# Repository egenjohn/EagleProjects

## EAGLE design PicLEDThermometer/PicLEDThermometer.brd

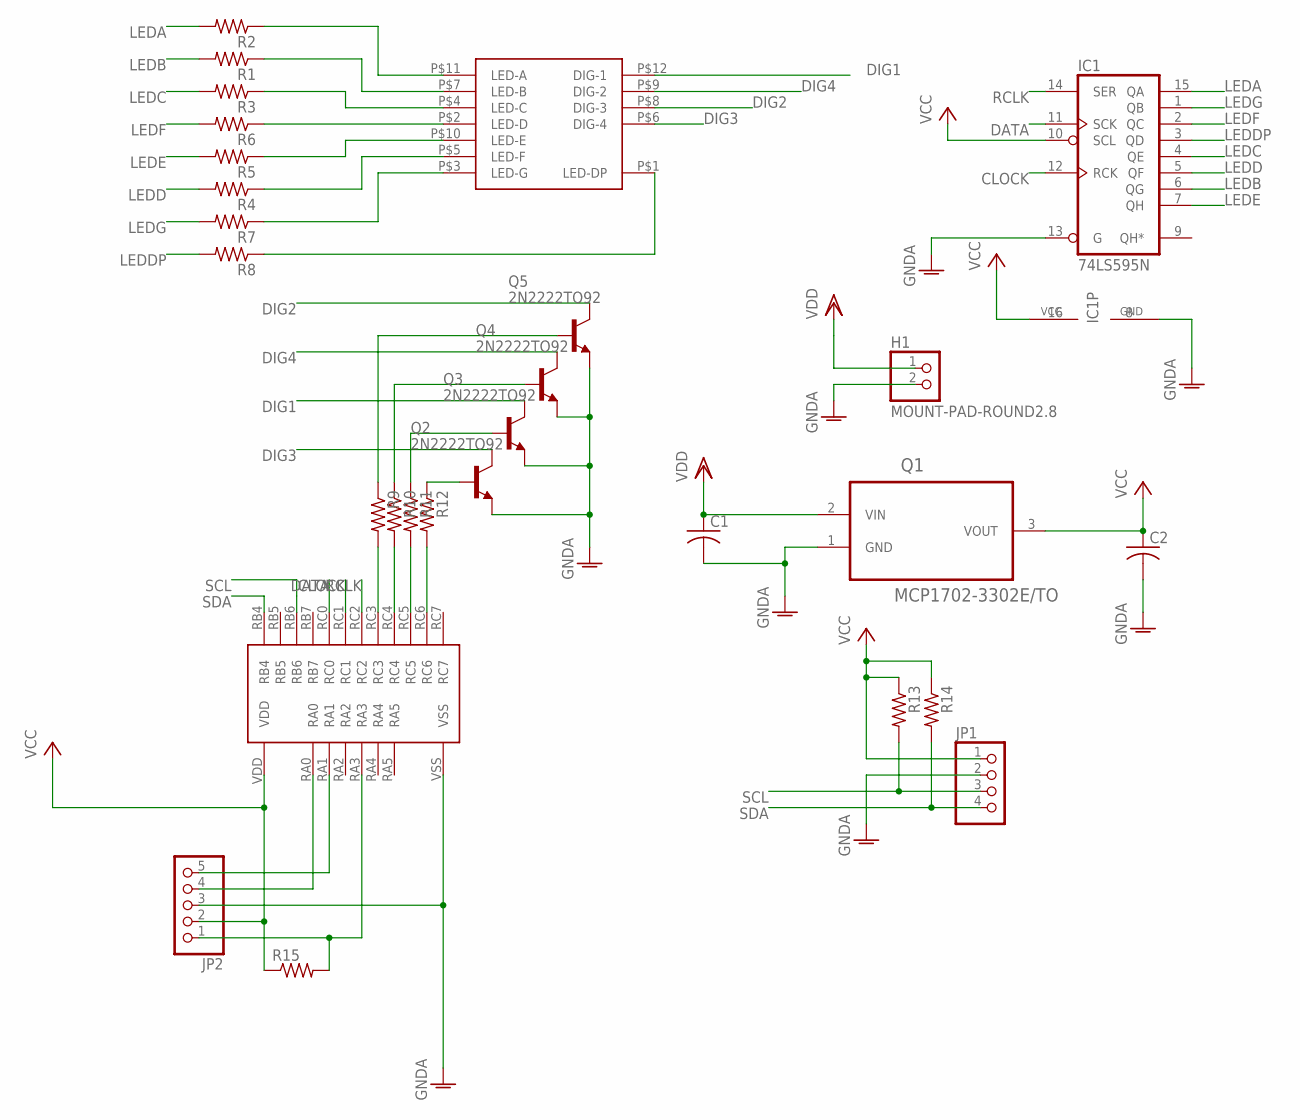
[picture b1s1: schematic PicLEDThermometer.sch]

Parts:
C1, C2: C-US025-030X050; C025-030X050
H1: MOUNT-PAD-ROUND2.8; 1X02
IC1: 74LS595N; DIL16
JP1: PINHD-1X4; 1X04
JP2: PINHD-1X5; 1X05
Q1: MCP1702-3302E/TO; TO127P254X533-3
Q2, Q3, Q4, Q5: 2N2222TO92; TO92-LINE
R1, R2, R3, R4, R5, R6, R7, R8, R9, R10, R11, R12, R13, R14, R15: R-US_0207/10; 0207/10
U$1: FYQ-5641
U$2: PIC16F1707

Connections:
CLOCK: IC1.12 (RCK), U$2.RC1
DATA: IC1.11 (SCK), U$2.RC0
DIG1: Q3.COL (C), U$1.P$12 (DIG-1)
DIG2: Q5.COL (C), U$1.P$8 (DIG-3)
DIG3: Q2.COL (C), U$1.P$6 (DIG-4)
DIG4: Q4.COL (C), U$1.P$9 (DIG-2)
GNDA: C1.2, C2.2, H1.2, IC1.8 (GND), IC1.13 (G), JP1.2, JP2.3, Q1.1 (GND), Q2.EMIT (E), Q3.EMIT (E), Q4.EMIT (E), Q5.EMIT (E), U$2.VSS
LEDA: IC1.15 (QA), R2.2
LEDB: IC1.6 (QG), R1.2
LEDC: IC1.4 (QE), R3.2
LEDD: IC1.5 (QF), R4.2
LEDDP: IC1.3 (QD), R8.2
LEDE: IC1.7 (QH), R5.2
LEDF: IC1.2 (QC), R6.2
LEDG: IC1.1 (QB), R7.2
unnamed: R2.1, U$1.P$11 (LED-A)
unnamed: R1.1, U$1.P$7 (LED-B)
unnamed: R3.1, U$1.P$4 (LED-C)
unnamed: R6.1, U$1.P$2 (LED-D)
unnamed: R5.1, U$1.P$10 (LED-E)
unnamed: R4.1, U$1.P$5 (LED-F)
unnamed: R7.1, U$1.P$3 (LED-G)
unnamed: JP2.1, R15.2, U$2.RA3
unnamed: JP2.4, U$2.RA0
unnamed: JP2.5, U$2.RA1
unnamed: R12.2, U$2.RC6
unnamed: R8.1, U$1.P$1 (LED-DP)
unnamed: R11.2, U$2.RC5
unnamed: R10.2, U$2.RC4
unnamed: R9.2, U$2.RC3
unnamed: Q2.BASE (B), R12.1
unnamed: Q3.BASE (B), R11.1
unnamed: Q4.BASE (B), R10.1
unnamed: Q5.BASE (B), R9.1
RCLK: IC1.14 (SER), U$2.RC2
SCL: JP1.3, R13.2, U$2.RB6
SDA: JP1.4, R14.2, U$2.RB4
VCC: C2.1, IC1.10 (SCL), IC1.16 (VCC), JP1.1, JP2.2, Q1.3 (VOUT), R13.1, R14.1, R15.1, U$2.VDD
VDD: C1.1, H1.1, Q1.2 (VIN)

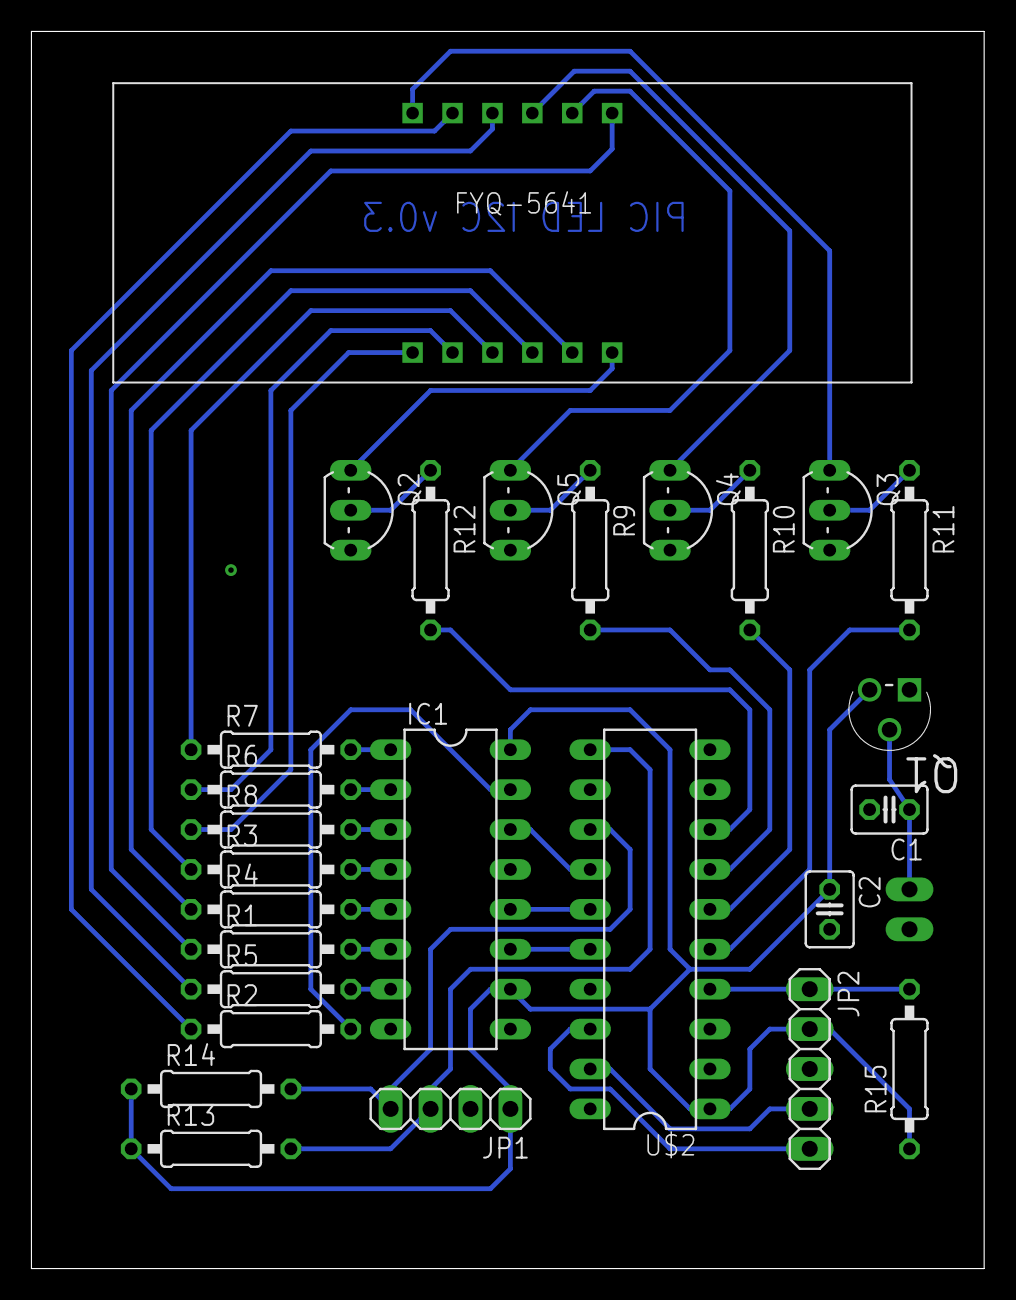
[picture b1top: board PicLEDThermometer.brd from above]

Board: 2 copper layers, 60.6 x 78.7 mm, 28 parts (1 on the bottom side), 39 nets.

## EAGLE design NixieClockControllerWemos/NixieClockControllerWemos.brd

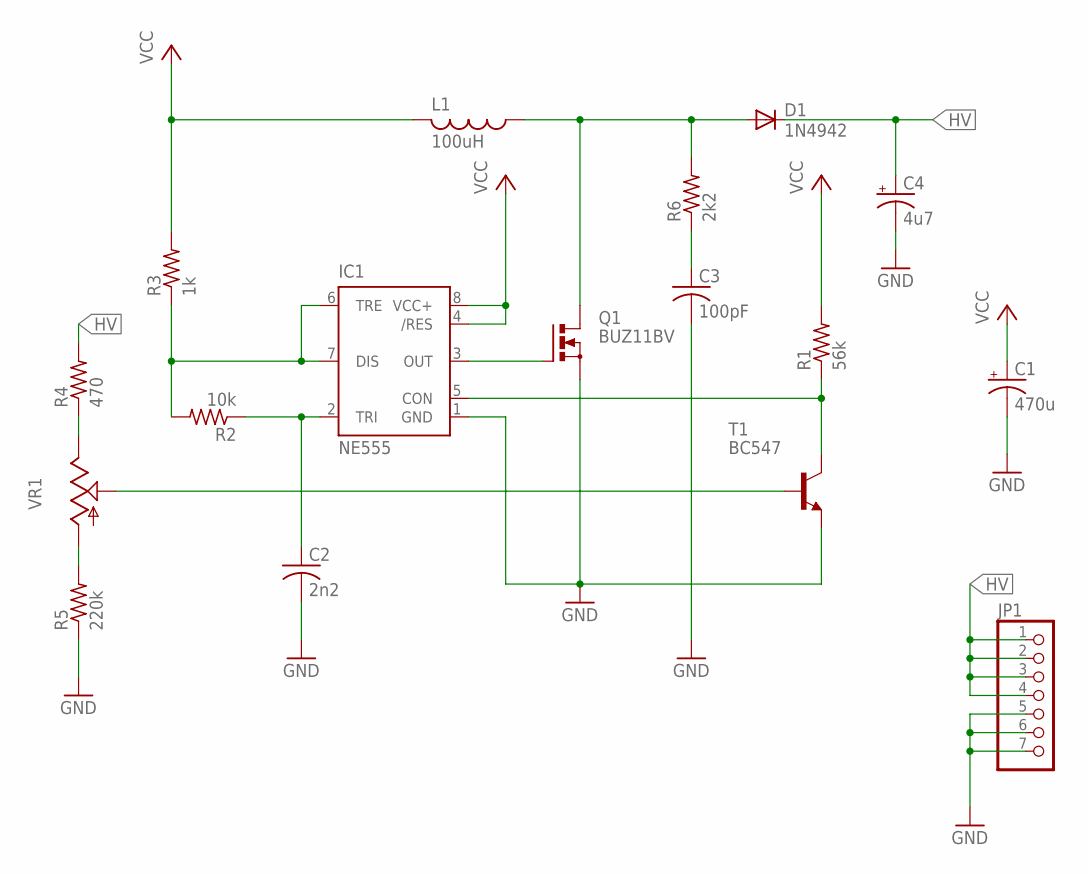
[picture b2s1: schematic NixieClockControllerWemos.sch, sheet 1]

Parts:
C1: 470u; E5-13
C2: 2n2; C050-025X075
C3: 100pF; C050-025X075
C4: 4u7; E3,5-8
D1: 1N4942; DO41-10
IC1: NE555; DIL-08
JP1: PINHD-1X7; 1X07
L1: 100uH; RLB0914
Q1: BUZ11BV; TO220BV
R1: 56k; 0207/10
R2: 10k; 0207/10
R3: 1k; 0207/10
R4: 470; 0207/10
R5: 220k; 0207/10
R6: 2k2; 0207/10
T1: BC547; TO92
VR1: TRIM_US-B25P; B25P

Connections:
GND: C1.-, C2.2, C3.2, C4.-, IC1.1 (GND), JP1.5, JP1.6, JP1.7, Q1.S, R5.1, T1.1 (E); also elsewhere on the board
HV: C4.+, D1.C, JP1.1, JP1.2, JP1.3, JP1.4, R4.2
unnamed: IC1.3 (OUT), Q1.G
unnamed: D1.A, L1.1, Q1.D, R6.2
unnamed: IC1.6 (TRE), IC1.7 (DIS), R2.2, R3.1
unnamed: R4.1, VR1.E
unnamed: IC1.5 (CON), R1.1, T1.3 (C)
unnamed: R5.2, VR1.A
unnamed: T1.2 (B), VR1.S
unnamed: C3.1, R6.1
unnamed: C2.1, IC1.2 (TRI), R2.1
VCC: C1.+, IC1.4 (/RES), IC1.8 (VCC+), L1.2, R1.2, R3.2; also elsewhere on the board

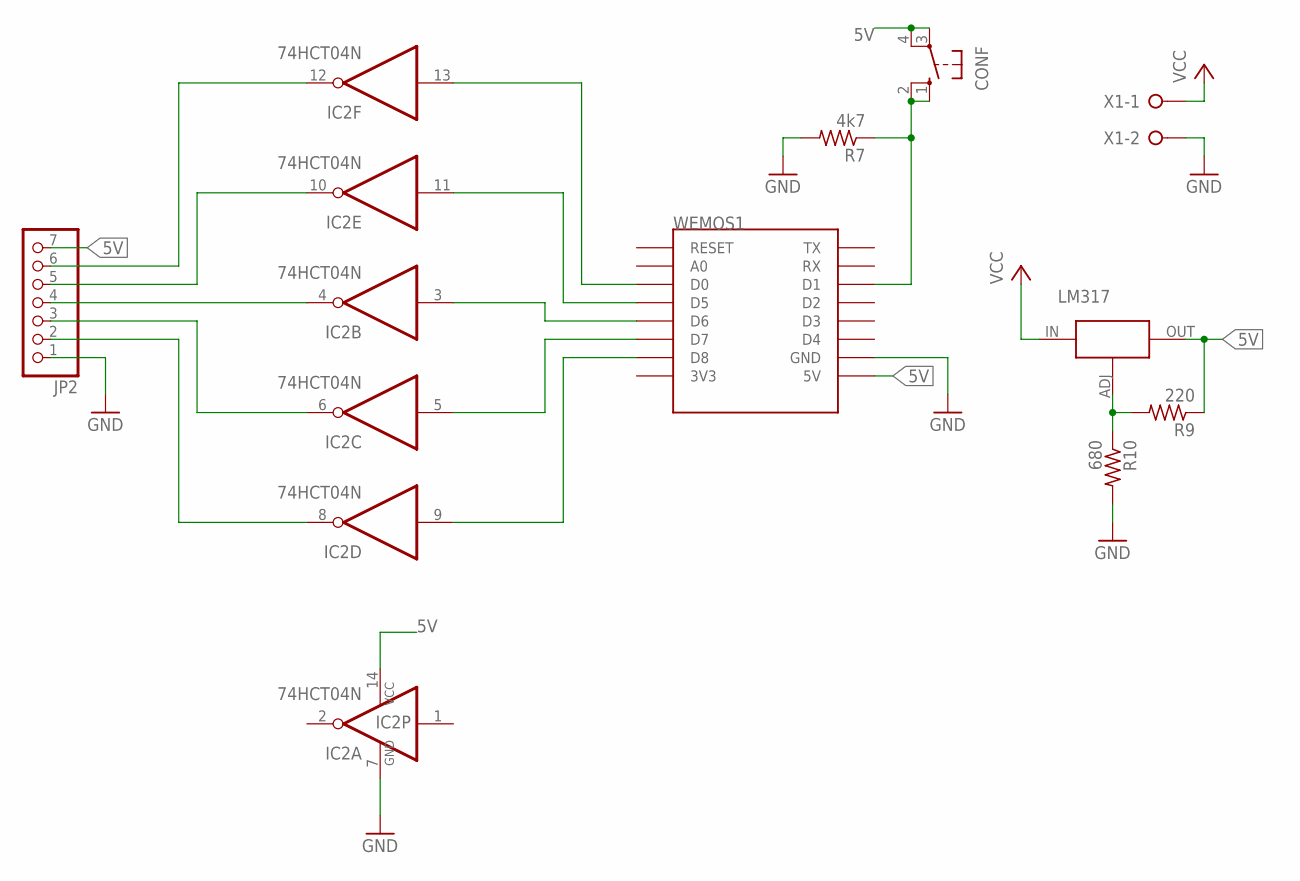
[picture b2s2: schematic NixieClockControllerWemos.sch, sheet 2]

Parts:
CONF: 10-XX; B3F-10XX
IC2: 74HCT04N; DIL14
JP2: PINHD-1X7; 1X07
R7: 4k7; 0207/10
R9: 220; 0207/10
R10: 680; 0207/10
U$3: LM317-TO220; LM317-TO220AV
WEMOS1: WEMOS-D1-MINI
X1: W237-02P; W237-132

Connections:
5V: CONF.3, CONF.4 (P1), IC2.14 (VCC), JP2.7, R9.1, U$3.OUT (VO), WEMOS1.5V
GND: IC2.7 (GND), JP2.1, R7.2, R10.2, WEMOS1.GND, X1.2; also elsewhere on the board
unnamed: IC2.12 (O), JP2.6
unnamed: IC2.10 (O), JP2.5
unnamed: R9.2, R10.1, U$3.ADJ
unnamed: IC2.4 (O), JP2.4
unnamed: IC2.6 (O), JP2.3
unnamed: IC2.8 (O), JP2.2
unnamed: CONF.1 (S), CONF.2 (S1), R7.1, WEMOS1.D1
unnamed: IC2.13 (I), WEMOS1.D0
unnamed: IC2.11 (I), WEMOS1.D5
unnamed: IC2.3 (I), WEMOS1.D6
unnamed: IC2.5 (I), WEMOS1.D7
unnamed: IC2.9 (I), WEMOS1.D8
VCC: U$3.IN (VI), X1.1; also elsewhere on the board

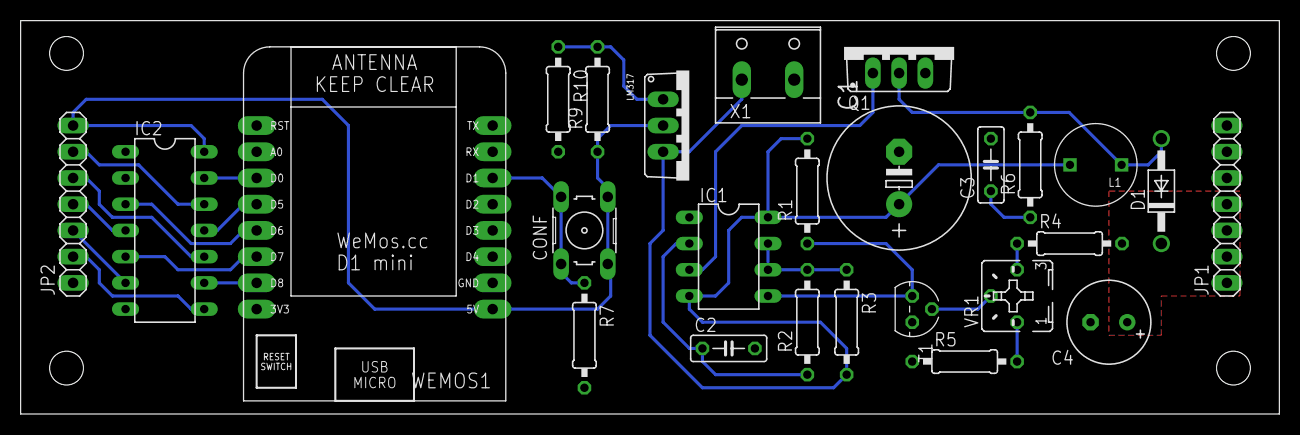
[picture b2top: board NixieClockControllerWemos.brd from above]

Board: 2 copper layers, 121.9 x 38.1 mm, 26 parts (0 on the bottom side), 25 nets.

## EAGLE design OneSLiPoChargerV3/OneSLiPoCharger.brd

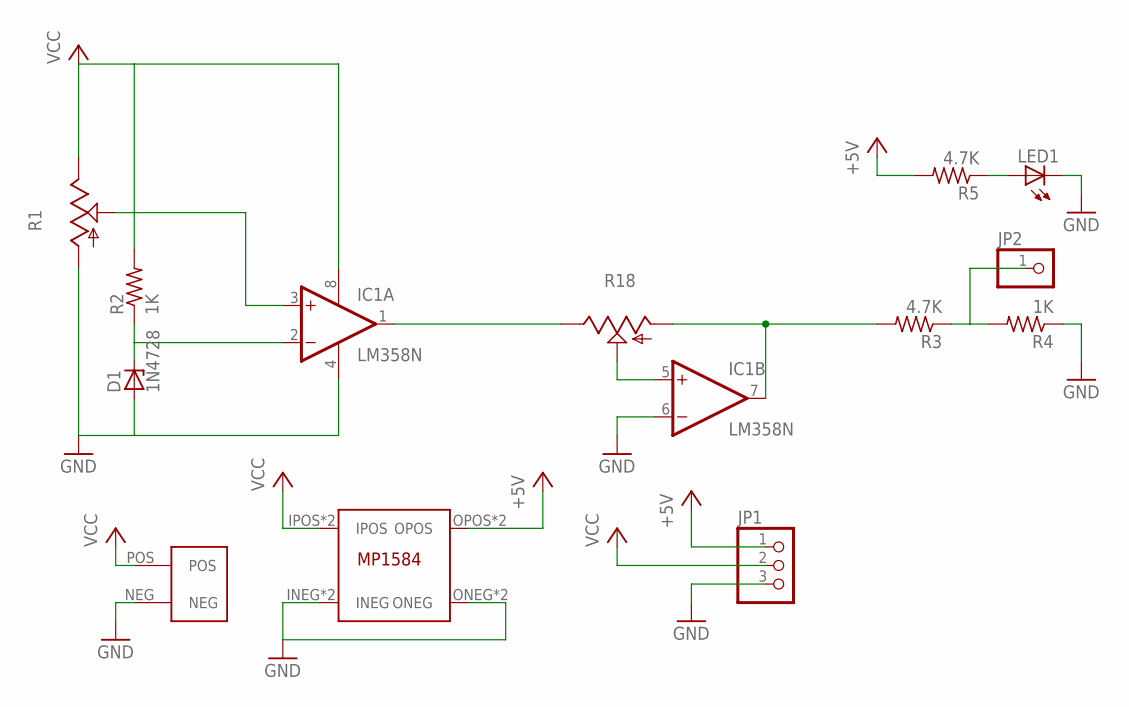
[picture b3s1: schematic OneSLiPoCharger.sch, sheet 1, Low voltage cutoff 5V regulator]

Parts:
D1: 1N4728; DO41Z10
IC1: LM358N; DIL08
JP1: PINHD-1X3; 1X03
JP2: PINHD-1X1; 1X01
LED1: LED3MM
R1, R18: TRIM_US-B25P; B25P
R2, R4: 1K; 0207/10
R3, R5: 4.7K; 0207/10
U$3: XT60
U$14: MP1584EN-MOD; MP1584MOD-TH

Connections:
+5V: JP1.1, R5.2, U$14.OPOS, U$14.OPOS1 (OPOS); also elsewhere on the board
GND: D1.A, IC1.4 (V-), IC1.6 (-IN), JP1.3, LED1.K (C), R1.A, R4.1, U$3.NEG, U$14.INEG, U$14.INEG1 (INEG), U$14.ONEG, U$14.ONEG1 (ONEG); also elsewhere on the board
unnamed: IC1.3 (+IN), R1.S
unnamed: JP2.1, R3.1, R4.2
unnamed: D1.C, IC1.2 (-IN), R2.1
unnamed: IC1.1 (OUT), R18.E
unnamed: IC1.7 (OUT), R3.2, R18.A
unnamed: LED1.A, R5.1
unnamed: IC1.5 (+IN), R18.S
VCC: IC1.8 (V+), JP1.2, R1.E, R2.2, U$3.POS, U$14.IPOS, U$14.IPOS1 (IPOS)

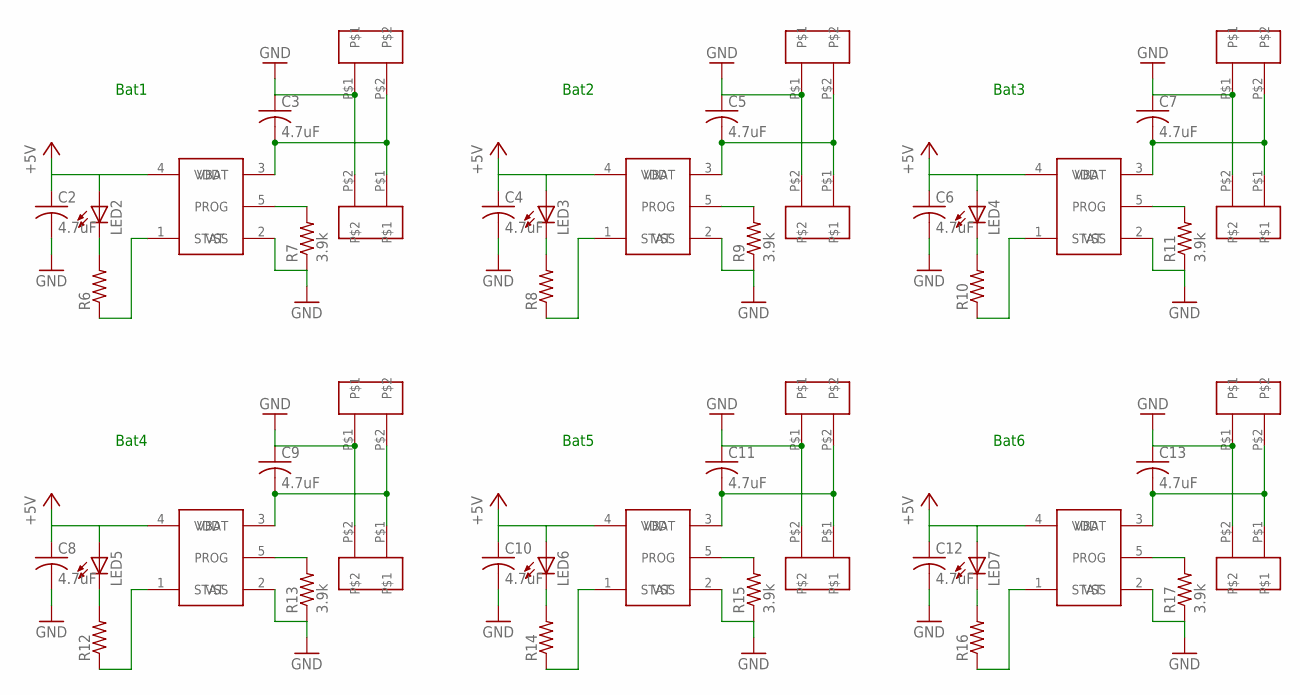
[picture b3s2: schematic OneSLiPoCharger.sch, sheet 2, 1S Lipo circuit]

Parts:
C2, C3, C4, C5, C6, C7, C8, C9, C10, C11, C12, C13: 4.7uF; C0805
LED2, LED3, LED4, LED5, LED6, LED7: LED3MM
R6, R8, R10, R12, R14, R16: R-US_M0805; M0805
R7, R9, R11, R13, R15, R17: 3.9k; M0805
U$1, U$4, U$6, U$8, U$10, U$12: MCP73831; MCP73831-SOT23
U$2, U$5, U$7, U$9, U$11, U$13: PICOBLADE-2PIN
U$15, U$16, U$17, U$18, U$19, U$20: JST-PH-2POS

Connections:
+5V: C2.1, C4.1, C6.1, C8.1, C10.1, C12.1, LED2.A, LED3.A, LED4.A, LED5.A, LED6.A, LED7.A, U$1.4 (VDD), U$4.4 (VDD), U$6.4 (VDD), U$8.4 (VDD), U$10.4 (VDD), U$12.4 (VDD); also elsewhere on the board
GND: C2.2, C3.1, C4.2, C5.1, C6.2, C7.1, C8.2, C9.1, C10.2, C11.1, C12.2, C13.1, R7.1, R9.1, R11.1, R13.1, R15.1, R17.1, U$1.2 (VSS), U$2.P$1, U$4.2 (VSS), U$5.P$1, U$6.2 (VSS), U$7.P$1, U$8.2 (VSS), U$9.P$1, U$10.2 (VSS), U$11.P$1, U$12.2 (VSS), U$13.P$1, U$15.P$2, U$16.P$2, U$17.P$2, U$18.P$2, U$19.P$2, U$20.P$2; also elsewhere on the board
unnamed: LED2.K (C), R6.2
unnamed: R6.1, U$1.1 (STAT)
unnamed: R7.2, U$1.5 (PROG)
unnamed: C3.2, U$1.3 (VBAT), U$2.P$2, U$15.P$1
unnamed: LED3.K (C), R8.2
unnamed: R8.1, U$4.1 (STAT)
unnamed: R9.2, U$4.5 (PROG)
unnamed: C5.2, U$4.3 (VBAT), U$5.P$2, U$16.P$1
unnamed: LED4.K (C), R10.2
unnamed: R10.1, U$6.1 (STAT)
unnamed: R11.2, U$6.5 (PROG)
unnamed: C7.2, U$6.3 (VBAT), U$7.P$2, U$17.P$1
unnamed: LED5.K (C), R12.2
unnamed: R12.1, U$8.1 (STAT)
unnamed: R13.2, U$8.5 (PROG)
unnamed: C9.2, U$8.3 (VBAT), U$9.P$2, U$20.P$1
unnamed: LED6.K (C), R14.2
unnamed: R14.1, U$10.1 (STAT)
unnamed: R15.2, U$10.5 (PROG)
unnamed: C11.2, U$10.3 (VBAT), U$11.P$2, U$19.P$1
unnamed: LED7.K (C), R16.2
unnamed: R16.1, U$12.1 (STAT)
unnamed: R17.2, U$12.5 (PROG)
unnamed: C13.2, U$12.3 (VBAT), U$13.P$2, U$18.P$1

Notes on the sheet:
Bat1
Bat2
Bat3
Bat4
Bat5
Bat6

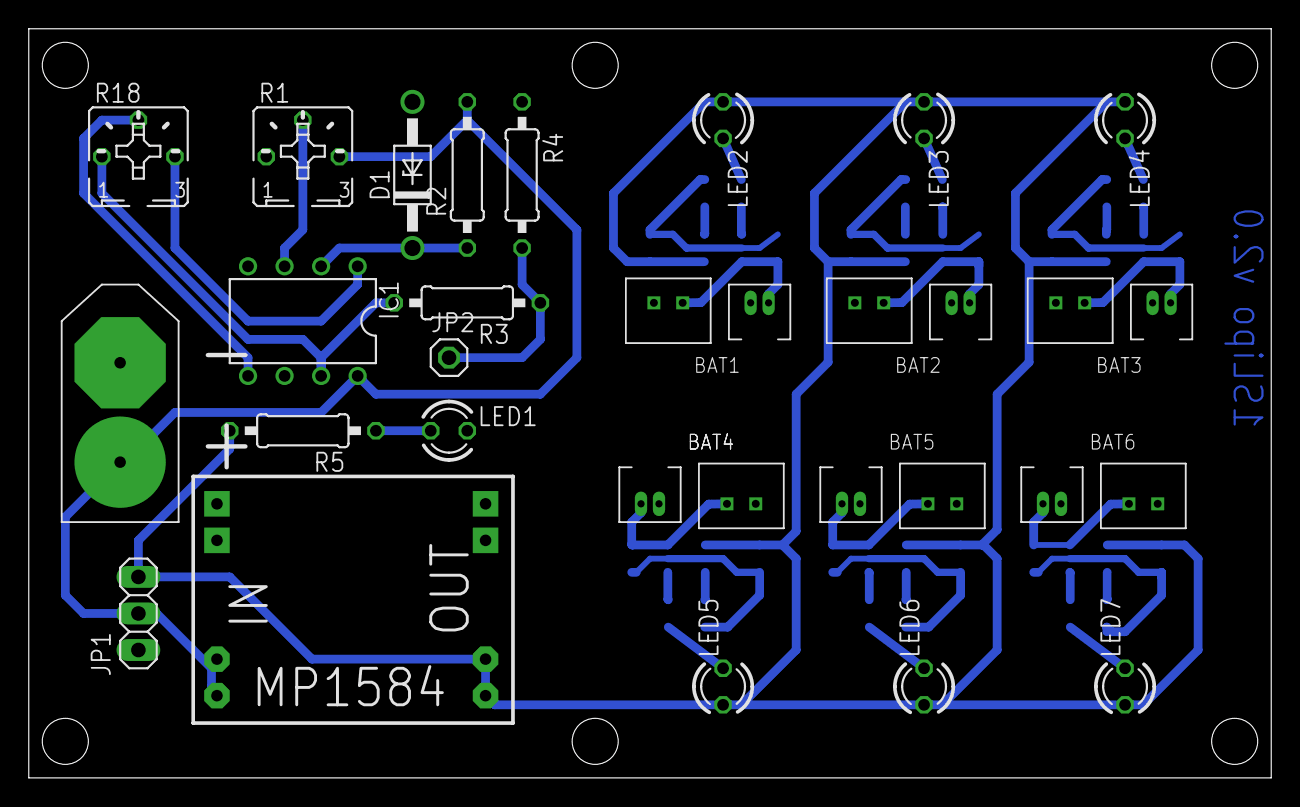
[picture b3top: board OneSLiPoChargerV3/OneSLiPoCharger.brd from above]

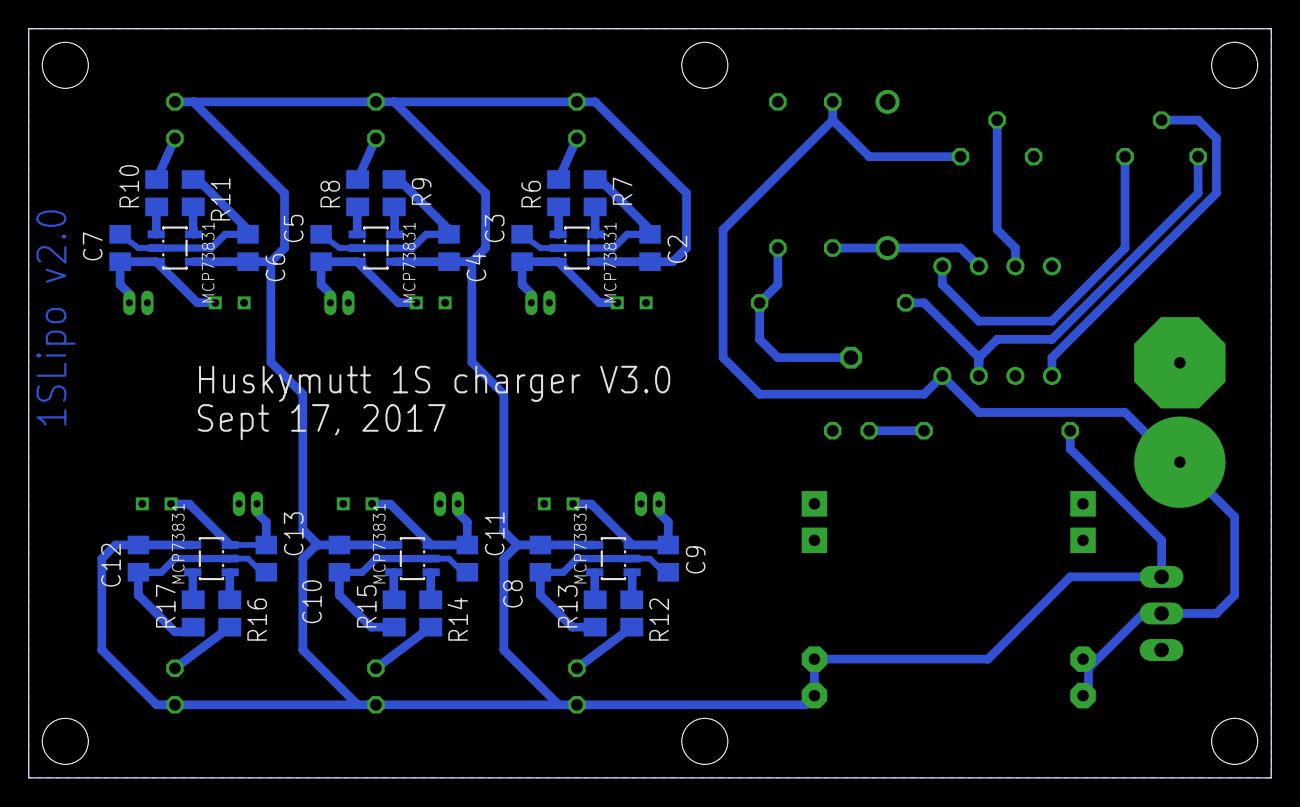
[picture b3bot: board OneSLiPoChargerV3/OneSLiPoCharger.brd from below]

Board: 2 copper layers, 86.4 x 52.1 mm, 62 parts (30 on the bottom side), 34 nets.

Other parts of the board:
DRILEGEND: DRILEGEND

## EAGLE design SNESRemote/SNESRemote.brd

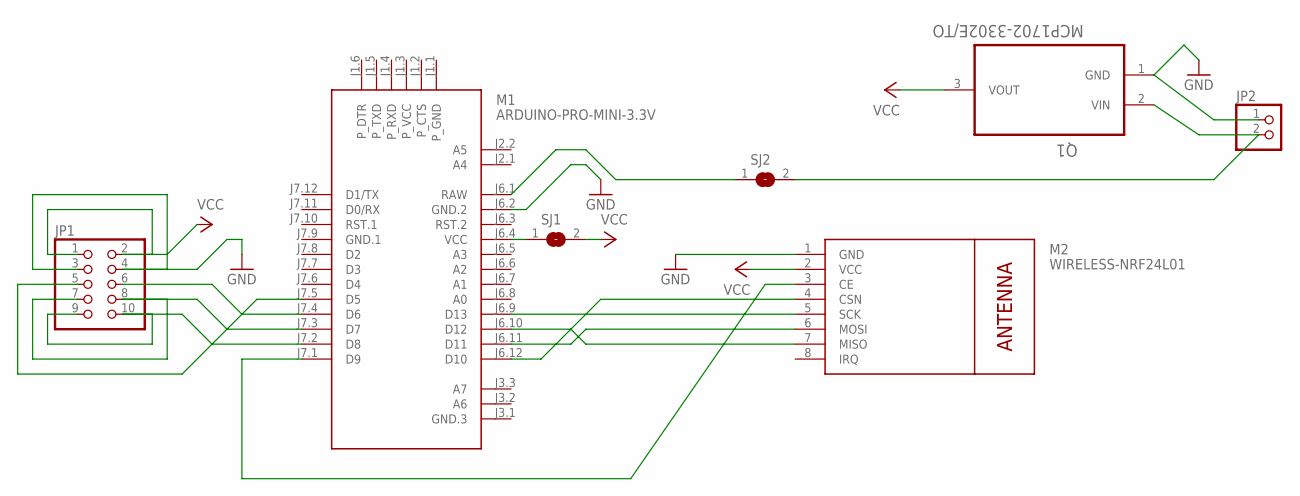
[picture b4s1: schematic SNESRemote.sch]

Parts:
JP1: PINHD-2X5; 2X05
JP2: PINHD-1X2; 1X02
M1: ARDUINO-PRO-MINI-3.3V; ARDUINO-PRO-MINI
M2: WIRELESS-NRF24L01
Q1: MCP1702-3302E/TO; TO127P254X533-3
SJ1, SJ2: SJ

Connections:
GND: JP1.3, JP1.4, JP2.1, M1.J6.2 (GND.2), M2.1 (GND), Q1.1 (GND)
GND.1: M1.J7.9 (GND.1)
unnamed: M1.J6.9 (D13), M2.5 (SCK)
unnamed: M1.J6.10 (D12), M2.7 (MISO)
unnamed: M1.J6.11 (D11), M2.6 (MOSI)
unnamed: M1.J6.12 (D10), M2.4 (CSN)
unnamed: M1.J7.1 (D9), M2.3 (CE)
unnamed: M1.J6.4 (VCC), SJ1.1
unnamed: M1.J6.1 (RAW), SJ2.1
unnamed: JP1.9, JP1.10, M1.J7.2 (D8)
unnamed: JP1.7, JP1.8, M1.J7.3 (D7)
unnamed: JP1.6, M1.J7.4 (D6)
unnamed: JP1.5, M1.J7.5 (D5)
unnamed: JP2.2, Q1.2 (VIN), SJ2.2
VCC: JP1.1, JP1.2, M2.2 (VCC), Q1.3 (VOUT), SJ1.2

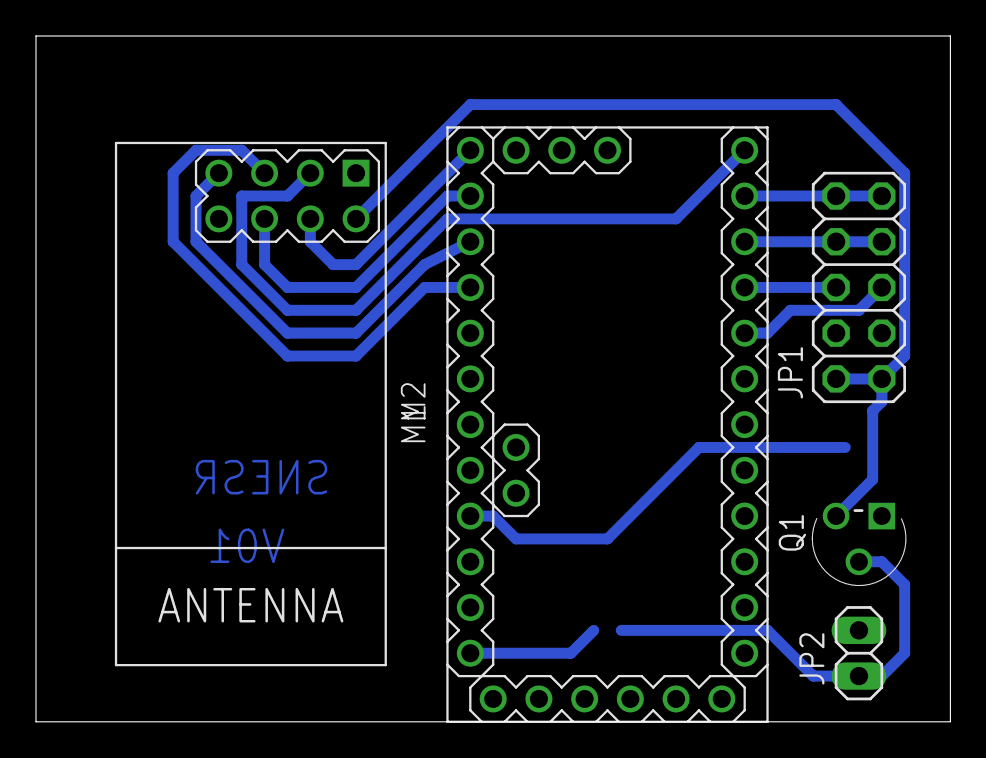
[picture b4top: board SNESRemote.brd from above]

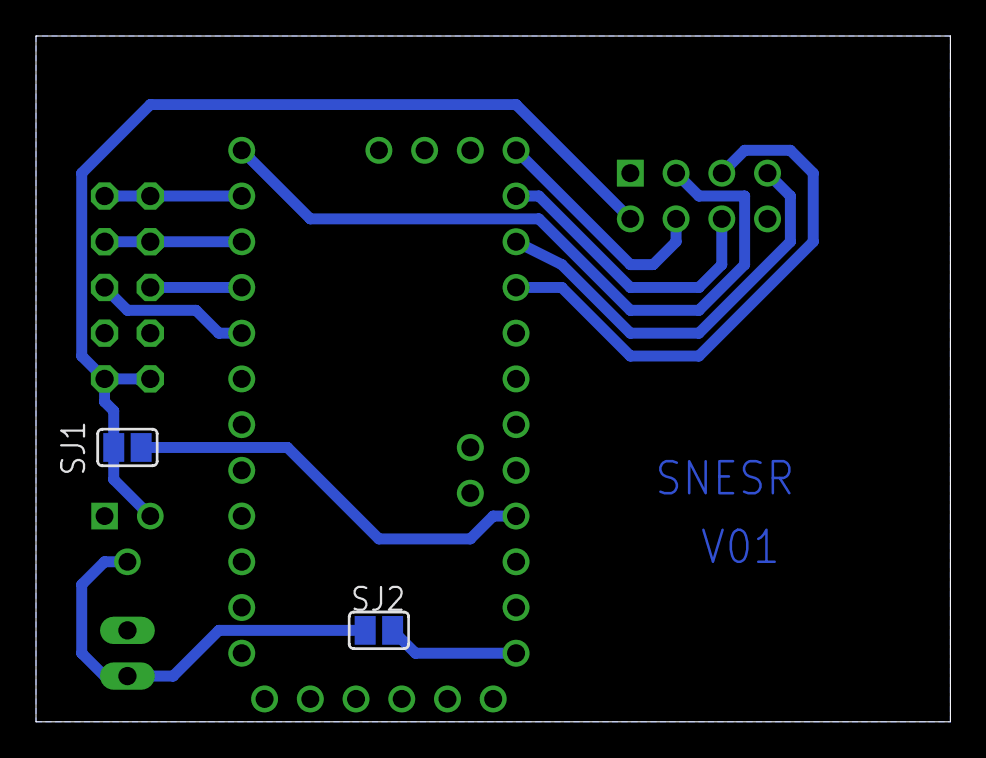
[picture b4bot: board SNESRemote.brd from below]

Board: 2 copper layers, 50.8 x 38.1 mm, 7 parts (2 on the bottom side), 14 nets.

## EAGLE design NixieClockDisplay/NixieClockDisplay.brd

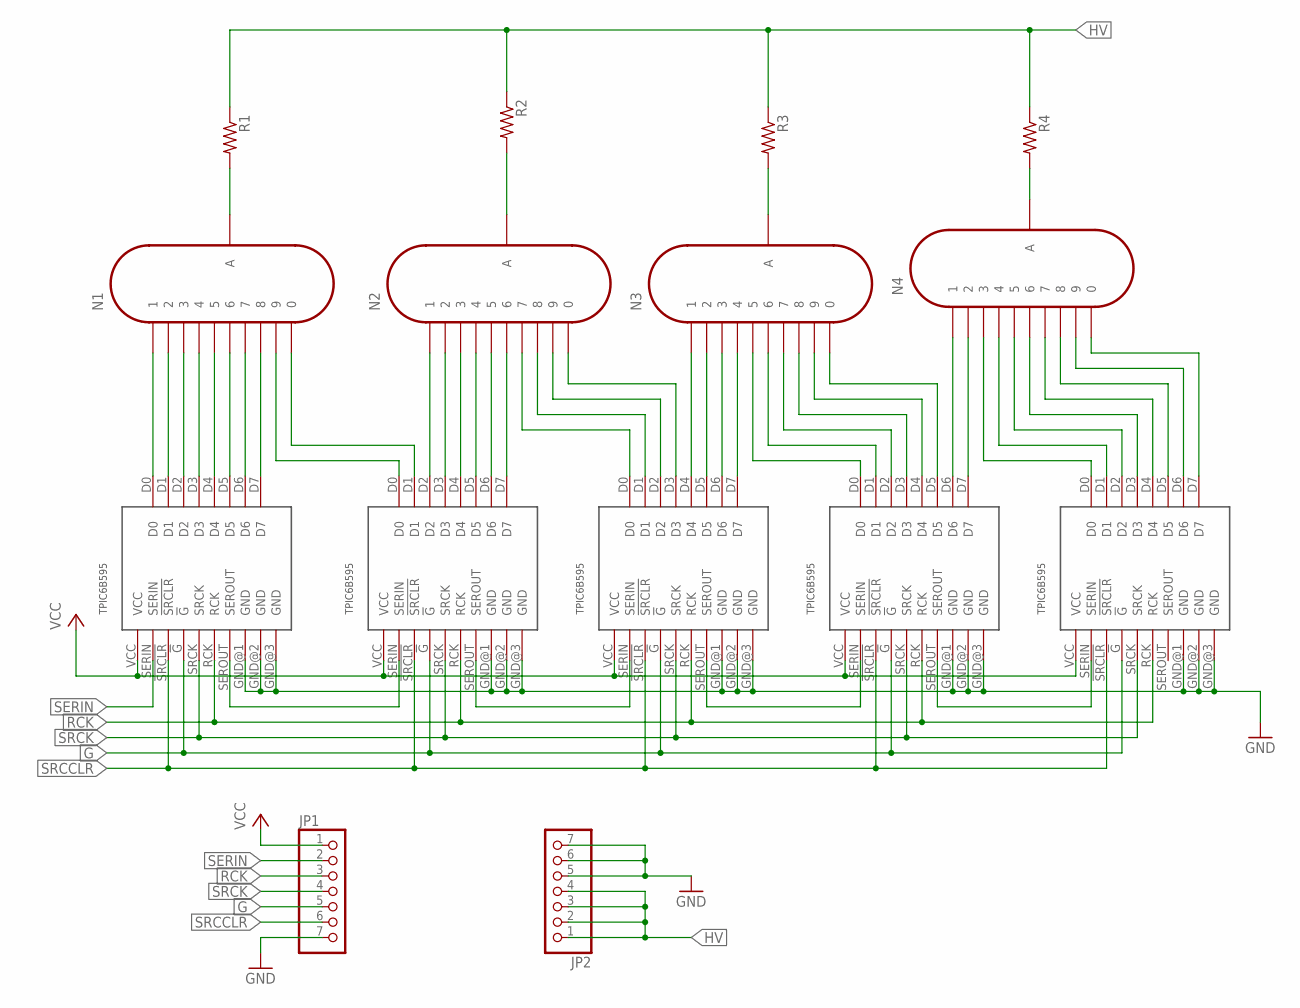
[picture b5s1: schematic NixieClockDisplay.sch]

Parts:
JP1, JP2: PINHD-1X7; 1X07
N1, N2, N3, N4: IN-12A; IN-12
R1, R2, R3, R4: R-US_0207/10; 0207/10
U$1, U$2, U$3, U$4, U$5: TPIC6B595; DIL20

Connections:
G: JP1.5, U$1.!G, U$2.!G, U$3.!G, U$4.!G, U$5.!G
GND: JP1.7, JP2.5, JP2.6, JP2.7, U$1.GND@1 (GND), U$1.GND@2 (GND), U$1.GND@3 (GND), U$2.GND@1 (GND), U$2.GND@2 (GND), U$2.GND@3 (GND), U$3.GND@1 (GND), U$3.GND@2 (GND), U$3.GND@3 (GND), U$4.GND@1 (GND), U$4.GND@2 (GND), U$4.GND@3 (GND), U$5.GND@1 (GND), U$5.GND@2 (GND), U$5.GND@3 (GND)
HV: JP2.1, JP2.2, JP2.3, JP2.4, R1.1, R2.1, R3.1, R4.1
unnamed: N1.A, R1.2
unnamed: N2.A, R2.2
unnamed: N3.A, R3.2
unnamed: N4.A, R4.2
unnamed: N1.1, U$1.D0
unnamed: N1.2, U$1.D1
unnamed: N1.3, U$1.D2
unnamed: N1.4, U$1.D3
unnamed: N1.5, U$1.D4
unnamed: N1.6, U$1.D5
unnamed: N1.7, U$1.D6
unnamed: N1.8, U$1.D7
unnamed: N1.9, U$2.D0
unnamed: N1.0, U$2.D1
unnamed: N2.1, U$2.D2
unnamed: N2.2, U$2.D3
unnamed: N2.3, U$2.D4
unnamed: N2.4, U$2.D5
unnamed: N2.5, U$2.D6
unnamed: N2.6, U$2.D7
unnamed: N2.7, U$3.D0
unnamed: N2.8, U$3.D1
unnamed: N2.9, U$3.D2
unnamed: N2.0, U$3.D3
unnamed: N3.1, U$3.D4
unnamed: N3.2, U$3.D5
unnamed: N3.3, U$3.D6
unnamed: N3.4, U$3.D7
unnamed: N3.5, U$4.D0
unnamed: N3.6, U$4.D1
unnamed: N3.7, U$4.D2
unnamed: N3.8, U$4.D3
unnamed: N3.9, U$4.D4
unnamed: N3.0, U$4.D5
unnamed: N4.1, U$4.D6
unnamed: N4.2, U$4.D7
unnamed: N4.3, U$5.D0
unnamed: N4.4, U$5.D1
unnamed: N4.5, U$5.D2
unnamed: N4.6, U$5.D3
unnamed: N4.7, U$5.D4
unnamed: N4.8, U$5.D5
unnamed: N4.9, U$5.D6
unnamed: N4.0, U$5.D7
unnamed: U$1.SEROUT, U$2.SERIN
unnamed: U$2.SEROUT, U$3.SERIN
unnamed: U$3.SEROUT, U$4.SERIN
unnamed: U$4.SEROUT, U$5.SERIN
RCK: JP1.3, U$1.RCK, U$2.RCK, U$3.RCK, U$4.RCK, U$5.RCK
SERIN: JP1.2, U$1.SERIN
SRCCLR: JP1.6, U$1.!SRCLR, U$2.!SRCLR, U$3.!SRCLR, U$4.!SRCLR, U$5.!SRCLR
SRCK: JP1.4, U$1.SRCK, U$2.SRCK, U$3.SRCK, U$4.SRCK, U$5.SRCK
VCC: JP1.1, U$1.VCC, U$2.VCC, U$3.VCC, U$4.VCC, U$5.VCC

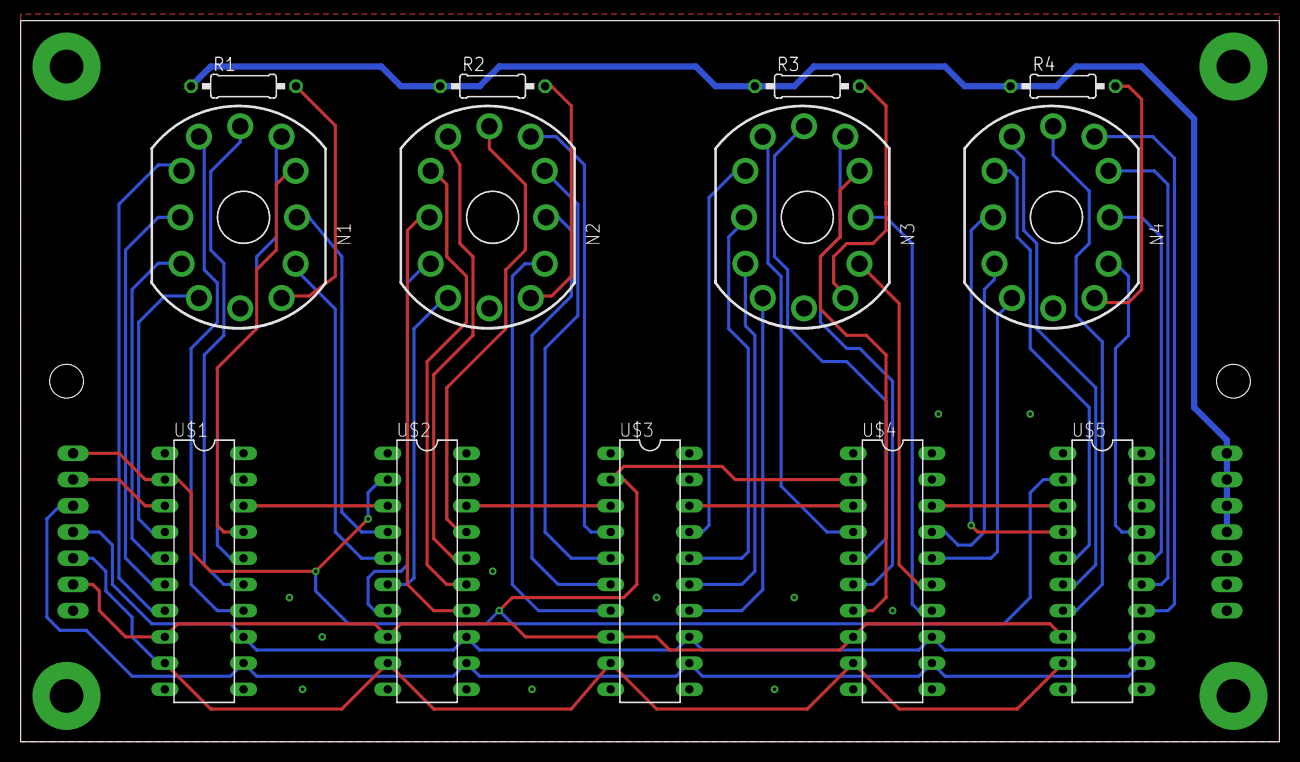
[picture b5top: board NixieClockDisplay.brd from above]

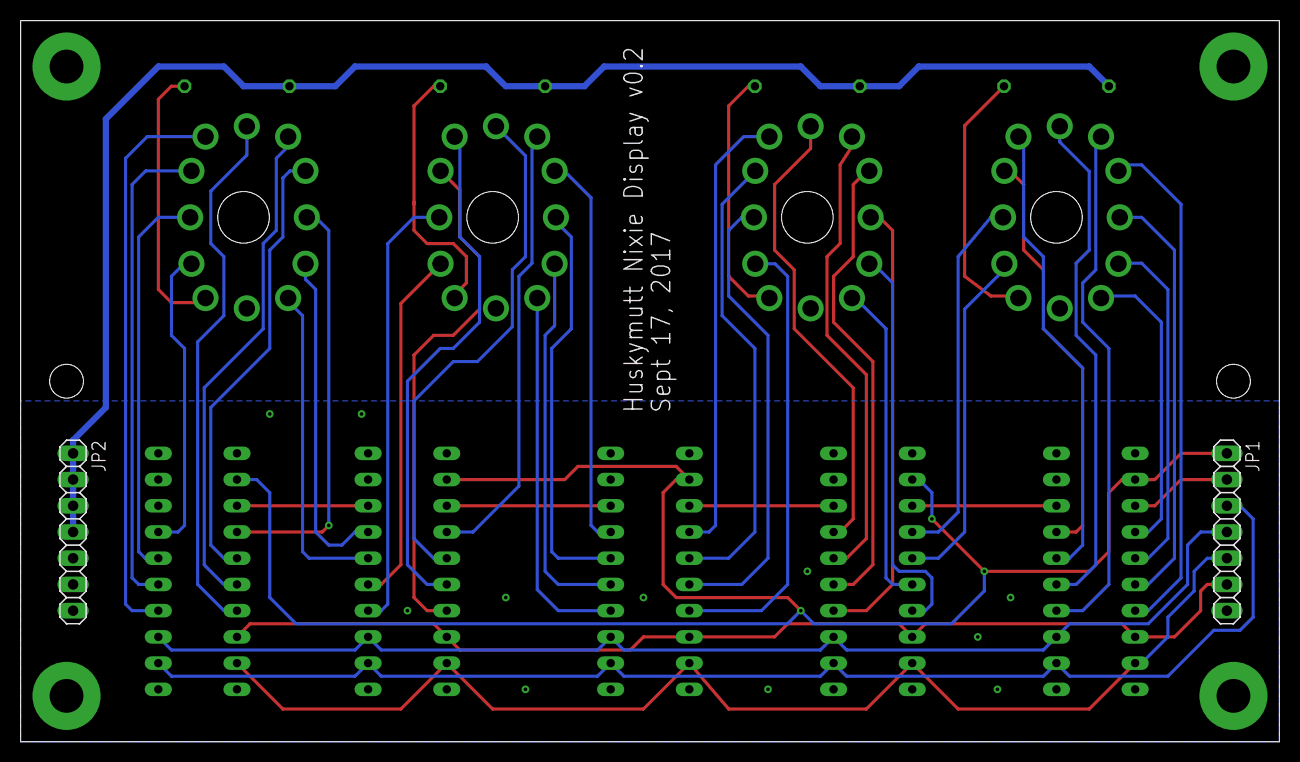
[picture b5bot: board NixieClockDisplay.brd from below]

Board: 2 copper layers, 121.9 x 69.8 mm, 15 parts (2 on the bottom side), 56 nets.

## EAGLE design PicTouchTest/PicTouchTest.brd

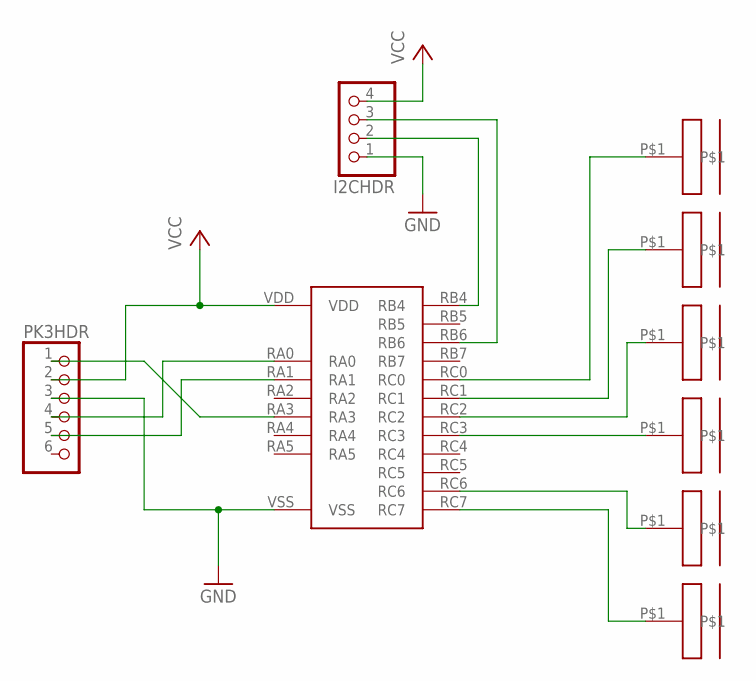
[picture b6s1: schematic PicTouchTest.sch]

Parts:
I2CHDR: PINHD-1X4; 1X04
PK3HDR: PINHD-1X6; 1X06
U$1: PIC16F1707
U$2, U$3, U$4, U$5, U$6, U$7: CAPTOUCH20MMRND; 20MMROUND

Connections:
GND: I2CHDR.1, PK3HDR.3, U$1.VSS
unnamed: PK3HDR.4, U$1.RA0
unnamed: PK3HDR.5, U$1.RA1
unnamed: PK3HDR.1, U$1.RA3
unnamed: U$1.RC0, U$2.P$1
unnamed: U$1.RC1, U$3.P$1
unnamed: U$1.RC2, U$4.P$1
unnamed: U$1.RC3, U$5.P$1
unnamed: U$1.RC6, U$6.P$1
unnamed: U$1.RC7, U$7.P$1
unnamed: I2CHDR.2, U$1.RB4
unnamed: I2CHDR.3, U$1.RB6
VCC: I2CHDR.4, PK3HDR.2, U$1.VDD

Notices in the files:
parts and their libraries:
diy-modules: Released under the Creative Commons Attribution 4.0 International License: http://creativecommons.org/licenses/by/4.0
